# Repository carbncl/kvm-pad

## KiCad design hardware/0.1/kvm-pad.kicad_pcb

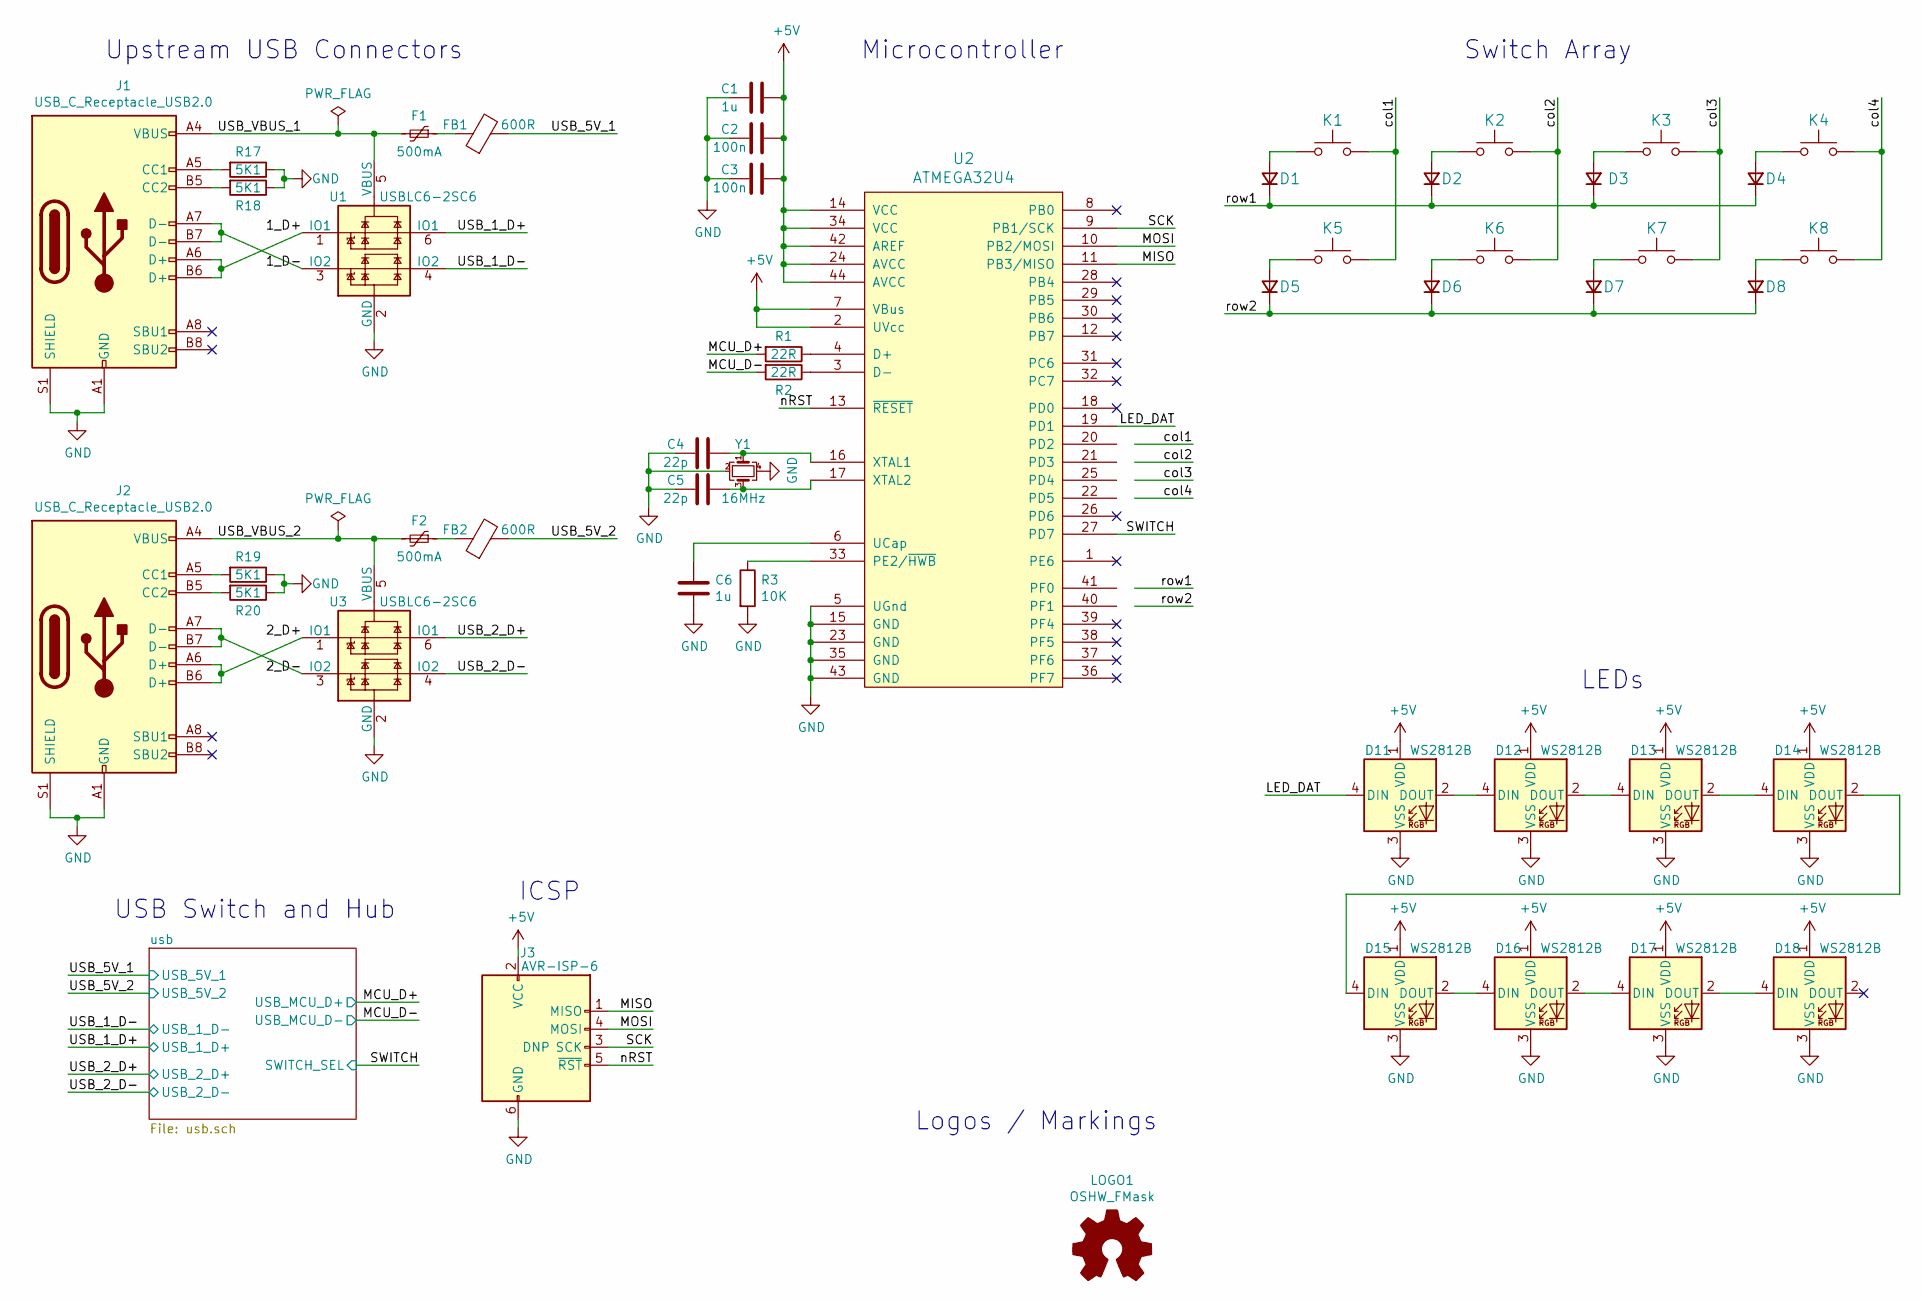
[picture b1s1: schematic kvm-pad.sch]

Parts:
C1, C6: 1u; C_0603_1608Metric
C2, C3: 100n; C_0603_1608Metric
C4, C5: 22p; C_0603_1608Metric
D1, D2, D3, D4, D5, D6, D7, D8: D; D_SOD-123; MPN 1N4148W-7-F; LCSC C83528
D11, D12, D13, D14, D15, D16, D17, D18: WS2812B; SK8612-MINI-E; MPN WS2812B; LCSC C114586
F1, F2: 500mA; Fuse_0805_2012Metric
FB1, FB2: 600R; Ferrite_Bead_0603
J1, J2: USB_C_Receptacle_USB2.0; USB_C_U262-161N-4BVC11
J3: AVR-ISP-6; AVR_PROG_2.54_SMT
K1, K2, K3, K4, K5, K6, K7, K8: KEYSW; Choc_Hotswap
LOGO1: OSHW_FMask; OSHW_Logo_3.6x3.6_F.Mask
R1, R2: 22R; R_0603_1608Metric
R3: 10K; R_0603_1608Metric
R17, R18, R19, R20: 5K1; R_0603_1608Metric
U1, U3: USBLC6-2SC6; SOT-23-6
U2: ATMEGA32U4; TQFP-44_10x10mm_P0.8mm
Y1: 16MHz; Crystal_SMD_3225-4Pin_3.2x2.5mm

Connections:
+5V: C1.1, C2.1, C3.1, D11.1 (VDD), D12.1 (VDD), D13.1 (VDD), D14.1 (VDD), D15.1 (VDD), D16.1 (VDD), D17.1 (VDD), D18.1 (VDD), J3.2 (VCC), U2.2 (UVcc), U2.7 (VBus), U2.14 (VCC), U2.24 (AVCC), U2.34 (VCC), U2.42 (AREF), U2.44 (AVCC); also elsewhere on the board
/1_D+: J1.A6 (D+), J1.B6 (D+), U1.1 (IO1)
/1_D-: J1.A7 (D-), J1.B7 (D-), U1.3 (IO2)
/2_D+: J2.A6 (D+), J2.B6 (D+), U3.1 (IO1)
/2_D-: J2.A7 (D-), J2.B7 (D-), U3.3 (IO2)
/LED_DAT: D11.4 (DIN), U2.19 (PD1)
/MCU_D+: R1.2; also elsewhere on the board
/MCU_D-: R2.2; also elsewhere on the board
/MISO: J3.1 (MISO), U2.11 (PB3/MISO)
/MOSI: J3.4 (MOSI), U2.10 (PB2/MOSI)
/SCK: J3.3 (SCK), U2.9 (PB1/SCK)
/SWITCH: U2.27 (PD7); also elsewhere on the board
/USB_1_D+: U1.6 (IO1); also elsewhere on the board
/USB_1_D-: U1.4 (IO2); also elsewhere on the board
/USB_2_D+: U3.6 (IO1); also elsewhere on the board
/USB_2_D-: U3.4 (IO2); also elsewhere on the board
/USB_5V_1: FB1.2; also elsewhere on the board
/USB_5V_2: FB2.2; also elsewhere on the board
/USB_VBUS_1: F1.2, J1.A4 (VBUS), J1.A9 (VBUS), J1.B4 (VBUS), J1.B9 (VBUS), U1.5 (VBUS)
/USB_VBUS_2: F2.2, J2.A4 (VBUS), J2.A9 (VBUS), J2.B4 (VBUS), J2.B9 (VBUS), U3.5 (VBUS)
/col1: K1.1, K5.1
/col2: K2.1, K6.1
/col3: K3.1, K7.1
/col4: K4.1, K8.1
/nRST: J3.5 (~RST), U2.13 (~RESET)
/row1: D1.1 (K), D2.1 (K), D3.1 (K), D4.1 (K)
/row2: D5.1 (K), D6.1 (K), D7.1 (K), D8.1 (K)
GND: C1.2, C2.2, C3.2, C4.2, C5.2, C6.2, D11.3 (VSS), D12.3 (VSS), D13.3 (VSS), D14.3 (VSS), D15.3 (VSS), D16.3 (VSS), D17.3 (VSS), D18.3 (VSS), J1.A1 (GND), J1.A12 (GND), J1.B1 (GND), J1.B12 (GND), J1.S1 (SHIELD), J2.A1 (GND), J2.A12 (GND), J2.B1 (GND), J2.B12 (GND), J2.S1 (SHIELD), J3.6 (GND), R3.2, R17.1, R18.1, R19.1, R20.1, U1.2 (GND), U2.5 (UGnd), U2.15 (GND), U2.23 (GND), U2.35 (GND), U2.43 (GND), U3.2 (GND), Y1.2, Y1.4; also elsewhere on the board
unnamed: C4.1, U2.16 (XTAL1), Y1.1
unnamed: C5.1, U2.17 (XTAL2), Y1.3
unnamed: C6.1, U2.6 (UCap)
unnamed: D1.2 (A), K1.2
unnamed: D2.2 (A), K2.2
unnamed: D3.2 (A), K3.2
unnamed: D4.2 (A), K4.2
unnamed: D5.2 (A), K5.2
unnamed: D6.2 (A), K6.2
unnamed: D7.2 (A), K7.2
unnamed: D8.2 (A), K8.2
unnamed: D11.2 (DOUT), D12.4 (DIN)
unnamed: D12.2 (DOUT), D13.4 (DIN)
unnamed: D13.2 (DOUT), D14.4 (DIN)
unnamed: D14.2 (DOUT), D15.4 (DIN)
unnamed: D15.2 (DOUT), D16.4 (DIN)
unnamed: D16.2 (DOUT), D17.4 (DIN)
unnamed: D17.2 (DOUT), D18.4 (DIN)
unnamed: F1.1, FB1.1
unnamed: F2.1, FB2.1
unnamed: J1.A5 (CC1), R17.2
unnamed: J1.B5 (CC2), R18.2
unnamed: J2.A5 (CC1), R19.2
unnamed: J2.B5 (CC2), R20.2
unnamed: R1.1, U2.4 (D+)
unnamed: R2.1, U2.3 (D-)
unnamed: R3.1, U2.33 (PE2/~HWB)

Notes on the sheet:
Logos / Markings
Upstream USB Connectors
USB Switch and Hub
Switch Array
ICSP
Microcontroller
LEDs

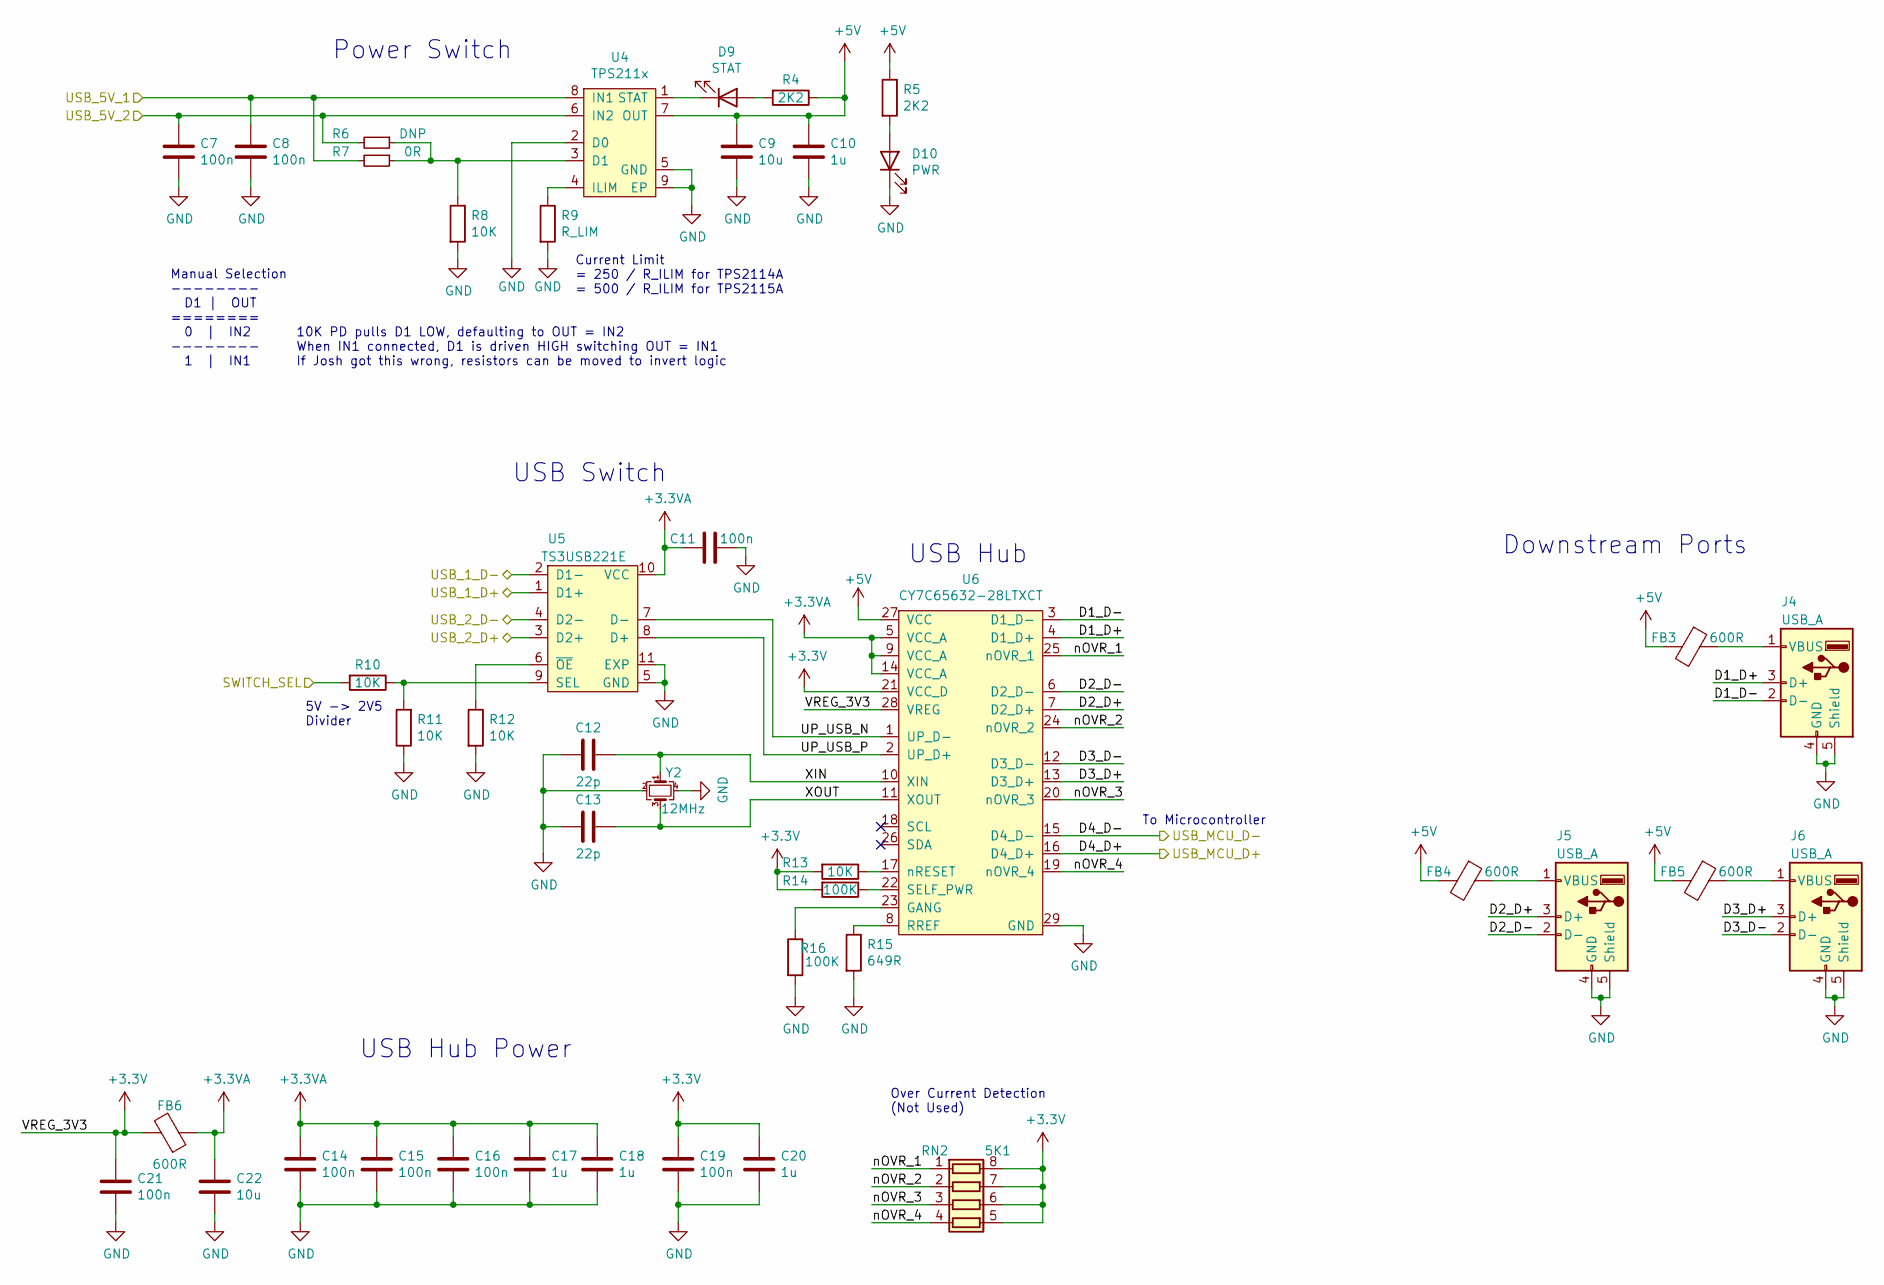
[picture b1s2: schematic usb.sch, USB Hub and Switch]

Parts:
C7, C8, C11: 100n; C_0603_1608Metric
C9: 10u; C_0603_1608Metric
C10: 1u; C_0603_1608Metric
C12, C13: 22p; C_0603_1608Metric; MPN CL10C220JB8NFNC; DigiKey 1276-2228-1-ND
C14, C15, C16, C19, C21: 100n; C_0603_1608Metric; MPN CL10B104KB8NNNC; DigiKey 1276-1000-1-ND
C17, C18, C20: 1u; C_0603_1608Metric; MPN CL10A105MP8NNNC; DigiKey 1276-1866-1-ND
C22: 10u; C_0603_1608Metric; MPN CL10A106MP8NNNC; DigiKey 1276-1871-1-ND
D9: STAT; LED_0603_1608Metric
D10: PWR; LED_0603_1608Metric
FB3, FB4, FB5: 600R; Ferrite_Bead_0603
FB6: 600R; Ferrite_Bead_0603; MPN BLM18AG601SN1D; LCSC C19330
J4, J5, J6: USB_A; USB_A_U234-051N-3GRA035-5
R4, R5: 2K2; R_0603_1608Metric
R6: DNP; R_0603_1608Metric
R7: 0R; R_0603_1608Metric
R8, R10, R11, R12: 10K; R_0603_1608Metric
R9: R_LIM; R_0603_1608Metric
R13: 10K; R_0603_1608Metric; MPN CR0603-JW-103ELF; DigiKey CR0603-JW-103ELFCT-ND
R14, R16: 100K; R_0603_1608Metric; MPN CR0603-JW-104ELF; DigiKey CR0603-JW-104ELFCT-ND
R15: 649R; R_0603_1608Metric; MPN MCR03ERTF6490; DigiKey RHM649CFCT-ND
RN2: 5K1; R_Array_Convex_4x0603; MPN RAVF164DJT10K0; DigiKey RAVF164DJT10K0CT-ND
U4: TPS211x; VSON-6-1EP_3x3mm_P0.65mm_EP1.65x2.4mm
U5: TS3USB221E; VSON-10-1EP_3x3mm_P0.5mm_EP1.65x2.4mm_ThermalVias
U6: CY7C65632-28LTXCT; QFN-28-1EP_5x5mm_P0.5mm_EP3.35x3.35mm_ThermalVias; MPN CY7C65632-28LTXCT; LCSC C466886
Y2: 12MHz; Crystal_SMD_3225-4Pin_3.2x2.5mm; MPN ABM8-12.000MHZ-B2-T; LCSC C276421

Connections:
+3.3VA: C11.2, C14.1, C15.1, C16.1, C17.1, C18.1, C22.1, FB6.1, U5.10 (VCC), U6.5 (VCC_A), U6.9 (VCC_A), U6.14 (VCC_A)
+3V3: C19.1, C20.1, C21.1, FB6.2, R13.2, R14.2, RN2.5 (R4.2), RN2.6 (R3.2), RN2.7 (R2.2), RN2.8 (R1.2), U6.21 (VCC_D), U6.28 (VREG)
+5V: C9.1, C10.1, FB3.2, FB4.2, FB5.2, R4.1, R5.1, U4.7 (OUT), U6.27 (VCC); also elsewhere on the board
/MCU_D+: U6.16 (D4_D+); also elsewhere on the board
/MCU_D-: U6.15 (D4_D-); also elsewhere on the board
/SWITCH: R10.2; also elsewhere on the board
/USB_1_D+: U5.1 (D1+); also elsewhere on the board
/USB_1_D-: U5.2 (D1-); also elsewhere on the board
/USB_2_D+: U5.3 (D2+); also elsewhere on the board
/USB_2_D-: U5.4 (D2-); also elsewhere on the board
/USB_5V_1: C8.1, R7.2, U4.8 (IN1); also elsewhere on the board
/USB_5V_2: C7.1, R6.2, U4.6 (IN2); also elsewhere on the board
/usb/D1_D+: J4.3 (D+), U6.4 (D1_D+)
/usb/D1_D-: J4.2 (D-), U6.3 (D1_D-)
/usb/D2_D+: J5.3 (D+), U6.7 (D2_D+)
/usb/D2_D-: J5.2 (D-), U6.6 (D2_D-)
/usb/D3_D+: J6.3 (D+), U6.13 (D3_D+)
/usb/D3_D-: J6.2 (D-), U6.12 (D3_D-)
/usb/UP_USB_N: U5.7 (D-), U6.1 (UP_D-)
/usb/UP_USB_P: U5.8 (D+), U6.2 (UP_D+)
/usb/XIN: C12.1, U6.10 (XIN), Y2.1
/usb/XOUT: C13.1, U6.11 (XOUT), Y2.3
/usb/nOVR_1: RN2.1 (R1.1), U6.25 (nOVR_1)
/usb/nOVR_2: RN2.2 (R2.1), U6.24 (nOVR_2)
/usb/nOVR_3: RN2.3 (R3.1), U6.20 (nOVR_3)
/usb/nOVR_4: RN2.4 (R4.1), U6.19 (nOVR_4)
GND: C7.2, C8.2, C9.2, C10.2, C11.1, C12.2, C13.2, C14.2, C15.2, C16.2, C17.2, C18.2, C19.2, C20.2, C21.2, C22.2, D10.1 (K), J4.4 (GND), J4.5 (Shield), J5.4 (GND), J5.5 (Shield), J6.4 (GND), J6.5 (Shield), R8.2, R9.2, R11.1, R12.2, R15.2, R16.2, U4.2 (D0), U4.5 (GND), U4.9 (EP), U5.5 (GND), U5.11 (EXP), U6.29 (GND), Y2.2, Y2.4; also elsewhere on the board
unnamed: D9.1 (K), U4.1 (STAT)
unnamed: D9.2 (A), R4.2
unnamed: D10.2 (A), R5.2
unnamed: FB3.1, J4.1 (VBUS)
unnamed: FB4.1, J5.1 (VBUS)
unnamed: FB5.1, J6.1 (VBUS)
unnamed: R6.1, R7.1, R8.1, U4.3 (D1)
unnamed: R9.1, U4.4 (ILIM)
unnamed: R10.1, R11.2, U5.9 (SEL)
unnamed: R12.1, U5.6 (~OE)
unnamed: R13.1, U6.17 (nRESET)
unnamed: R14.1, U6.22 (SELF_PWR)
unnamed: R15.1, U6.8 (RREF)
unnamed: R16.1, U6.23 (GANG)

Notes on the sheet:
USB Hub
USB Hub Power
Over Current Detection (Not Used)
To Microcontroller
Downstream Ports
Current Limit = 250 / R_ILIM for TPS2114A = 500 / R_ILIM for TPS2115A
Power Switch
Manual Selection -------- D1 | OUT ======== 0 | IN2 -------- 1 | IN1
10K PD pulls D1 LOW, defaulting to OUT = IN2 When IN1 connected, D1 is driven HIGH switching OUT = IN1 If Josh got this wrong, resistors can be moved to invert logic
5V -> 2V5 Divider
USB Switch

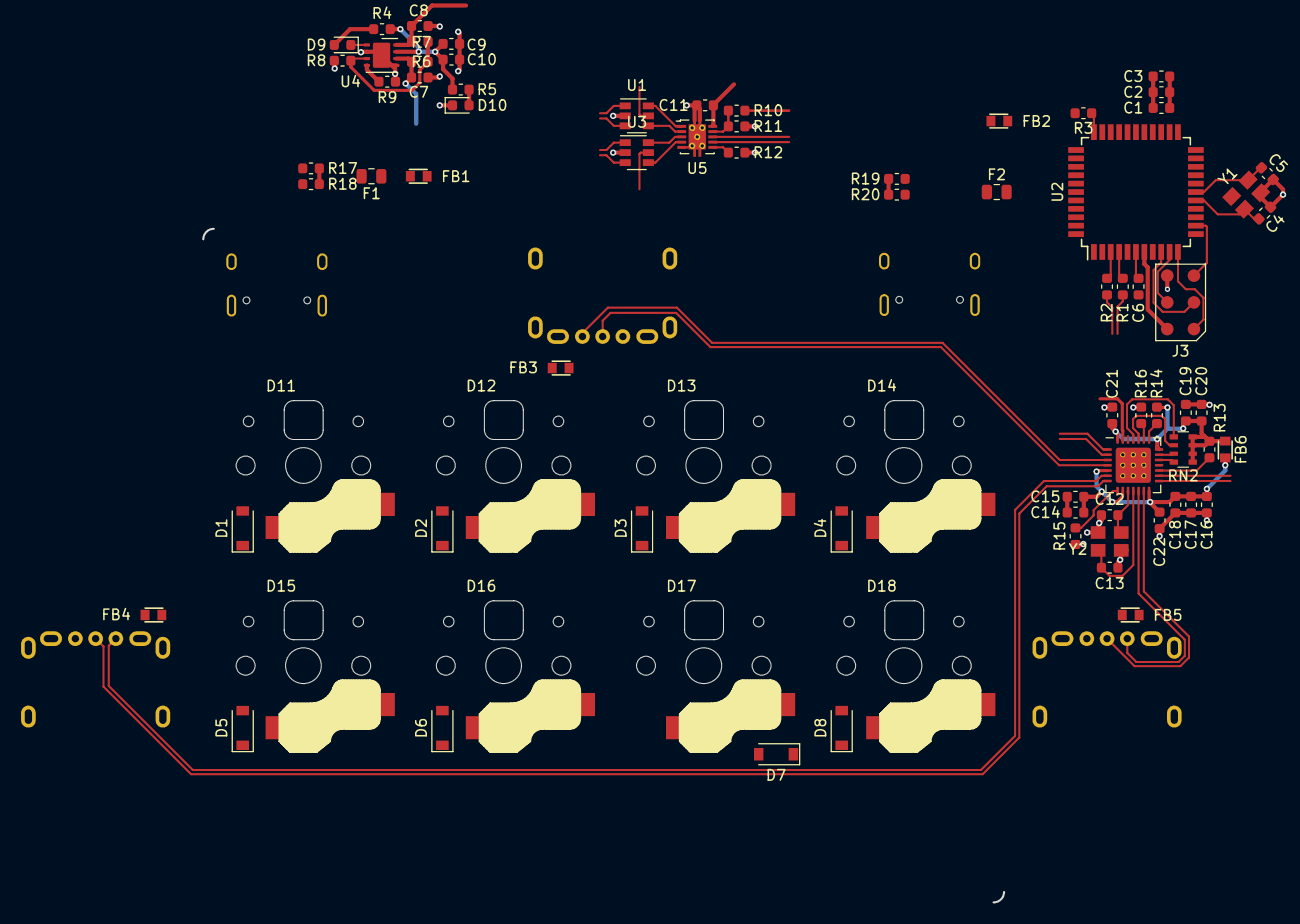
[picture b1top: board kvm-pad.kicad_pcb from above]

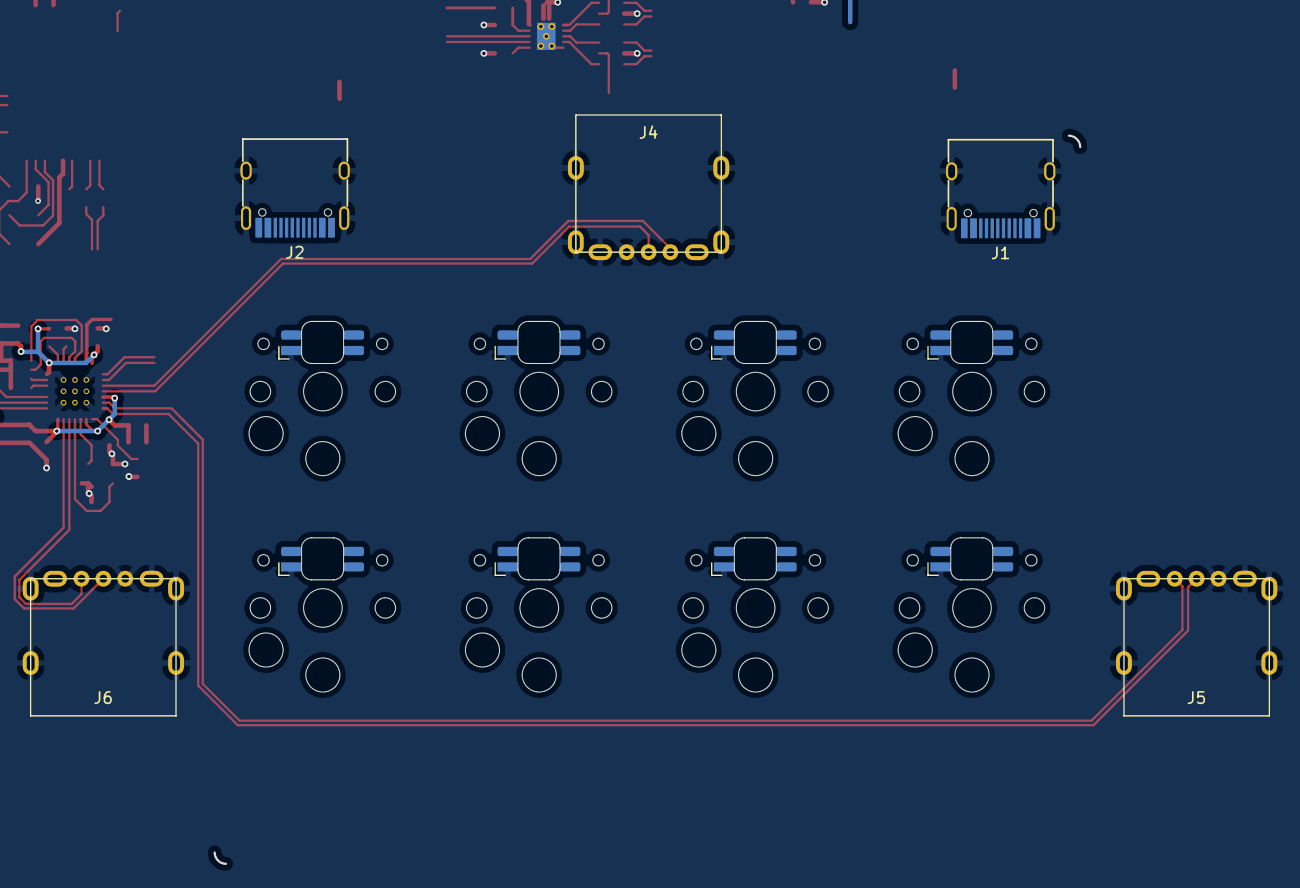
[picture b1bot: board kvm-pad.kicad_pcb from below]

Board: 2 copper layers, 92 parts (5 on the bottom side), 85 nets.

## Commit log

2020-06-07 init repo
2020-06-07 usb section done
2020-06-07 update mask gap to 50 um
2020-06-19 add mcu + 2x4 switches + icsp
2020-06-20 update jkl with led footprints
2020-06-27 Add missing footprints
2020-06-27 Update jkl & footprints
    USBA / Kailh Choc / ATMEGA32U4-AU
2020-06-27 Add RGB LEDs
2020-06-28 Update jkl, adjust schema accordingly, 32u4+16MHz
2020-06-28 Clean up WS2812 routing
2020-07-18 WIP PCB Layout with parts grouped
2020-07-20 Switch to VSON TS3USB221E for easier routing
2020-07-20 [pcb] Switch routing
2020-07-20 [pcb] Hub routing
2020-07-20 [sch][pcb] Swap USBLC6 IOs for easing PCB routing
2020-07-20 [sch] Remove lost +5V
2020-07-20 [pcb] Power switch routing
2020-07-20 [pcb] Switch RN1 to 4xR
2020-07-20 [pcb] Small edits
2020-07-20 [pcb] MCU routing
2020-07-26 [pcb] More routing
    Also add a GND plane on bottom
2020-07-28 [pcb] Hub routing
    Decoupling + crystal are high priority and moved closer to
    Also fixed various things
2020-07-28 [pcb] Layouting
2020-08-04 alt layout
    following what usb says... ;p
